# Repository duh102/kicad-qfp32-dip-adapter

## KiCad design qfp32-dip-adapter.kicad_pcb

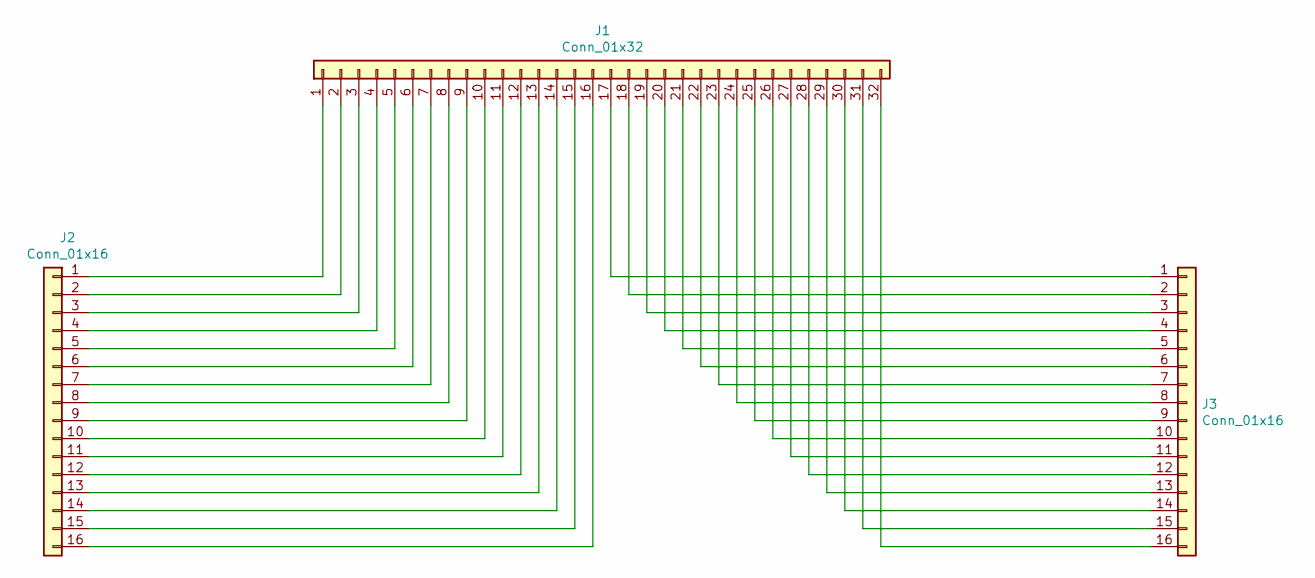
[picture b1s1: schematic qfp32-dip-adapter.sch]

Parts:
J1: Conn_01x32; QFP_Socket-32_Yamaichi_IC51-0324-1498
J2, J3: Conn_01x16; PinHeader_1x16_P2.54mm_Vertical

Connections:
unnamed: J1.1, J2.1
unnamed: J1.2, J2.2
unnamed: J1.3, J2.3
unnamed: J1.4, J2.4
unnamed: J1.5, J2.5
unnamed: J1.6, J2.6
unnamed: J1.7, J2.7
unnamed: J1.8, J2.8
unnamed: J1.9, J2.9
unnamed: J1.10, J2.10
unnamed: J1.11, J2.11
unnamed: J1.12, J2.12
unnamed: J1.13, J2.13
unnamed: J1.14, J2.14
unnamed: J1.15, J2.15
unnamed: J1.16, J2.16
unnamed: J1.17, J3.1
unnamed: J1.18, J3.2
unnamed: J1.19, J3.3
unnamed: J1.20, J3.4
unnamed: J1.21, J3.5
unnamed: J1.22, J3.6
unnamed: J1.23, J3.7
unnamed: J1.24, J3.8
unnamed: J1.25, J3.9
unnamed: J1.26, J3.10
unnamed: J1.27, J3.11
unnamed: J1.28, J3.12
unnamed: J1.29, J3.13
unnamed: J1.30, J3.14
unnamed: J1.31, J3.15
unnamed: J1.32, J3.16

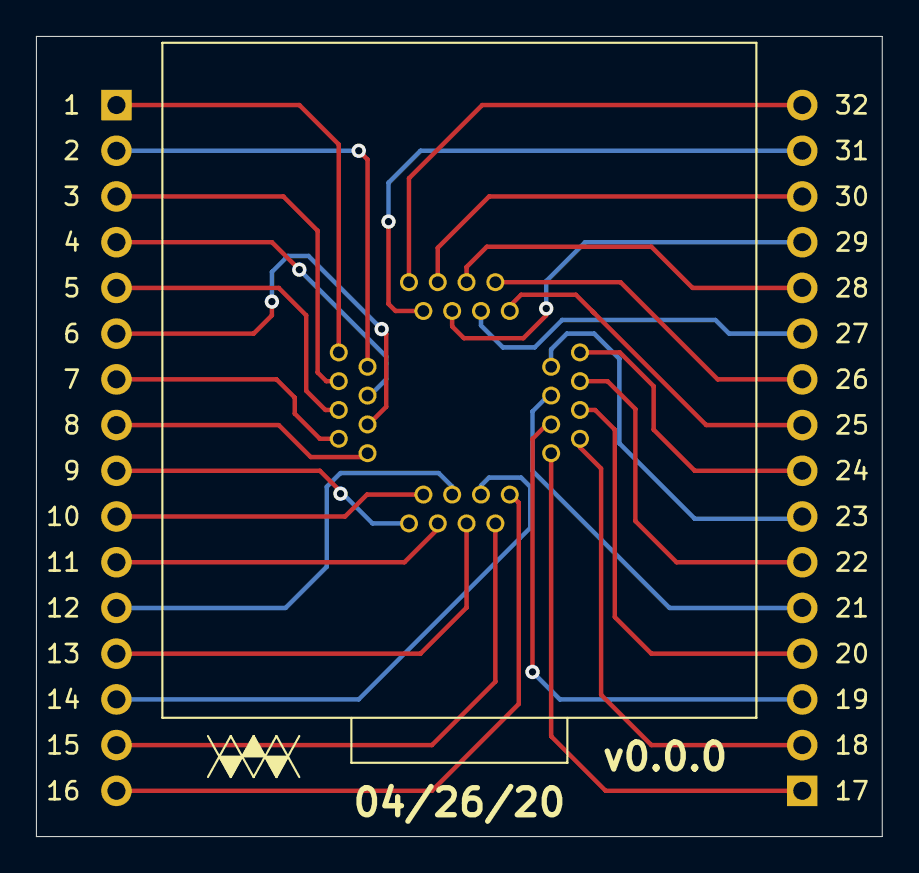
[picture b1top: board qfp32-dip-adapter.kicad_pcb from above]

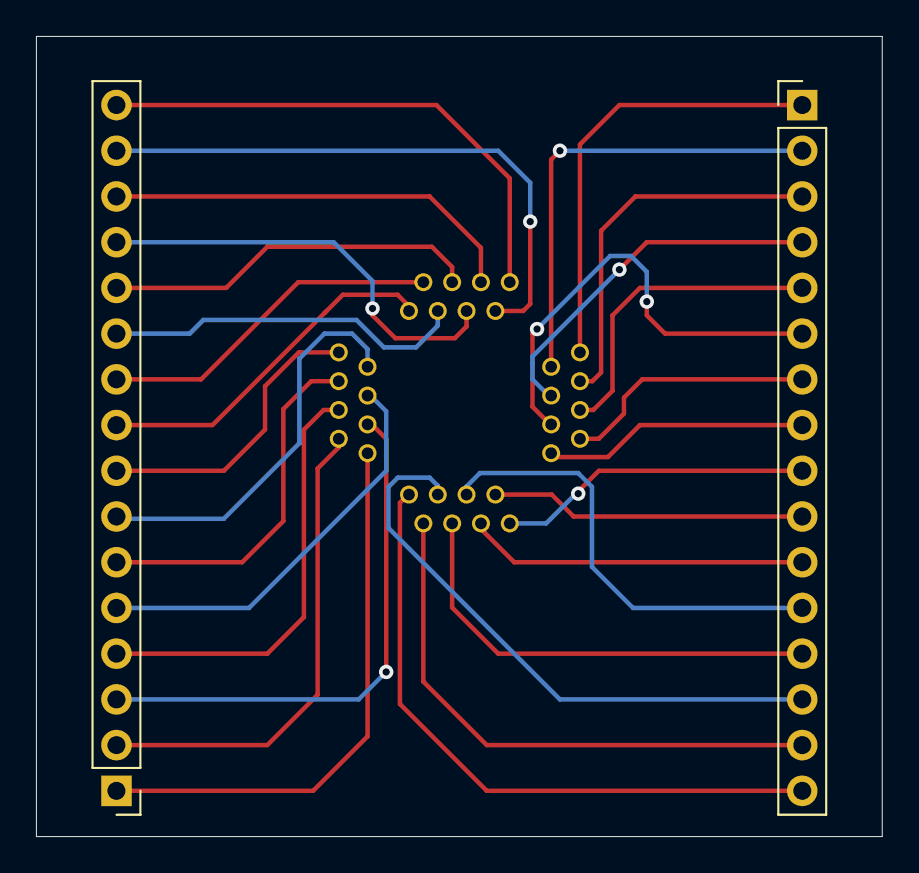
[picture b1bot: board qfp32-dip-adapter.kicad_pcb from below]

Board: 2 copper layers, 47.0 x 44.5 mm, 3 parts (2 on the bottom side), 32 nets.
